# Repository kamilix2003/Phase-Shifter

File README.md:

# Interface for MAPS-010144 digital phase shifter

## Description

STM32G0B01 based board for controlling daisy-chained digital phase shifter via SPI-like serial interface. User can interface with the board either by buttons and LEDs on the board or via virtual serial port over USB, communication over serial port is realized using simple TLV protocol. The board is providing bipolar supply for the phase shifters.

<!--  -->

### Repository contents
- [KiCAD](KiCAD) - ECAD projects of all desinged PCBs for the project
- [python_api](python_api) - Simple python api for communicating with the controller via serial port
- [Src](Src) - Firmware source code separated from generated STM32 project
- [phase_shifter_measurements](phase_shifter_mesurements) - Measuremented scattering parameters of the phase shifter

## Firmware 

<!--  -->

### Serial communication

Available commands:
| **T**ype | **L**ength [bytes] | **V**alue             | Description |
|----------|--------------------|-----------------------|-------------|
| 0x02     | 1                  | command id            | Ack         |
| 0x10     | 4                  | phase shifts (0 - 15) | Set phase   |
| 0x11     | 0                  | -                     | Transmit    |
| 0x12     | 1                  | latch state           | Latch state |

After each message microcontroller should send ACK message with payload containing command id of original message

Example routine to set new phase delay:
1. `0x12 0x01 0x00` - make sure that latch is set low in order to accept data via serial interface
1. `0x10 0x04 0x04 0x02 0x0f 0x08` - send phase shifts to the controller
1. `0x11 0x00` - transmit phase shifts via SPI to the phase shifters
1. `0x12 0x01 0x01` - set latch to update phase shift 
1. `0x12 0x01 0x00` - reset latch

### Buttons and LEDs

The board is equiped in 3 tactile buttons and two 4-led displays where each display shows according to the silkscreen description either currently selected phase shifter or phase shift set for the selected phase shifter.
Buttons have following functions starting from the left most button:
- On short press transmits current phase shifter configuration over SPI
- On short press cycles through 4 phase shifters, on long press sets all phase shifters to 0
- On short press increments phase delay, on long press set current phase shifter to 0

<!-- # MAPS-010144 Phase Shifter Interface as Part of Phased Antenna Array

## Description

A microcontroller serves as an interface for phase control, managing multiple phase shifters connected in a daisy chain via SPI. Bidirectional communication between the PC and MCU is established via UART/USB.

## Goals

in **bold** features in scope of SKM project

- **Serial interface with IC via SPI peripheral**
- **PC-MCU communication by UART/USB (virtual COM)**
- **Controlling multiple phase shifter in daisy chain**
- Python API for controlling beam direction
- I2C bus for communication with multiple arrays where one becomes master

## Block diagram

## Docs

- [Specification](./docs/Specification.md)
- [Report](./docs/SKM_Report_Kamil_Chaj.pdf) -->

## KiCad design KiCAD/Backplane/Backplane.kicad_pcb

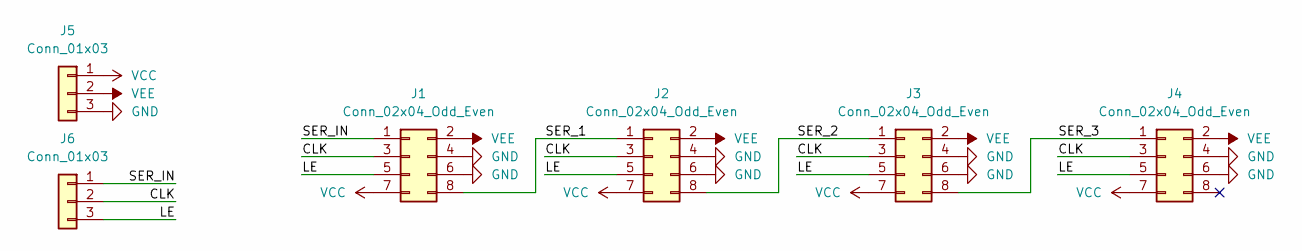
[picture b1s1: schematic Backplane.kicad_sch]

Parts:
J1, J2, J3, J4: Conn_02x04_Odd_Even; PinSocket_2x04_P2.54mm_Vertical
J5, J6: Conn_01x03; PinHeader_1x03_P2.54mm_Horizontal

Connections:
/CLK: J1.3, J2.3, J3.3, J4.3, J6.2
/LE: J1.5, J2.5, J3.5, J4.5, J6.3
/SER_1: J1.8, J2.1
/SER_2: J2.8, J3.1
/SER_3: J3.8, J4.1
/SER_IN: J1.1, J6.1
GND: J1.4, J1.6, J2.4, J2.6, J3.4, J3.6, J4.4, J4.6, J5.3
VCC: J1.7, J2.7, J3.7, J4.7, J5.1
VEE: J1.2, J2.2, J3.2, J4.2, J5.2

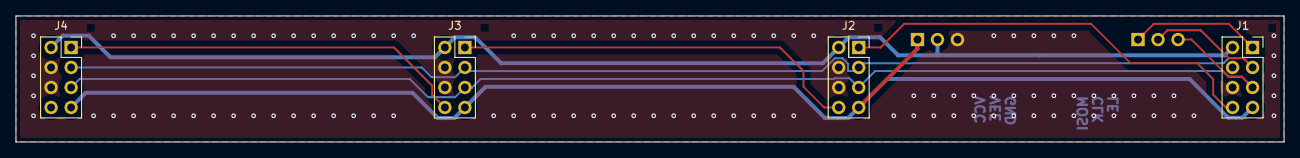
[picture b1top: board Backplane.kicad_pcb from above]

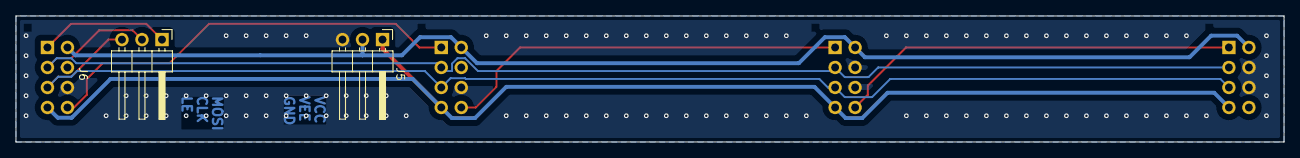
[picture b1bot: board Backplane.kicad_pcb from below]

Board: 2 copper layers, 161.0 x 16.0 mm, 6 parts (2 on the bottom side), 9 nets.

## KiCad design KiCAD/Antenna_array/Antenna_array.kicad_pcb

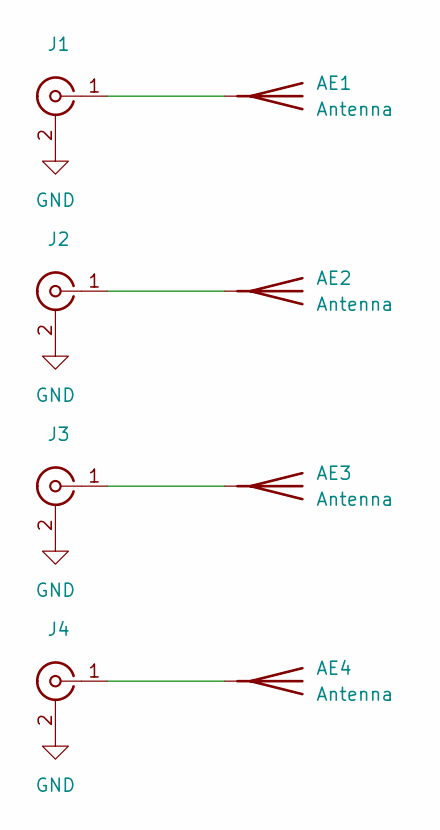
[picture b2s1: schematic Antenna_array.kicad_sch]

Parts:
AE1, AE2, AE3, AE4: Antenna; patch
J1, J2, J3, J4: Conn

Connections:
GND: J1.2, J2.2, J3.2, J4.2
unnamed: AE1.1 (A), J1.1
unnamed: AE2.1 (A), J2.1
unnamed: AE3.1 (A), J3.1
unnamed: AE4.1 (A), J4.1

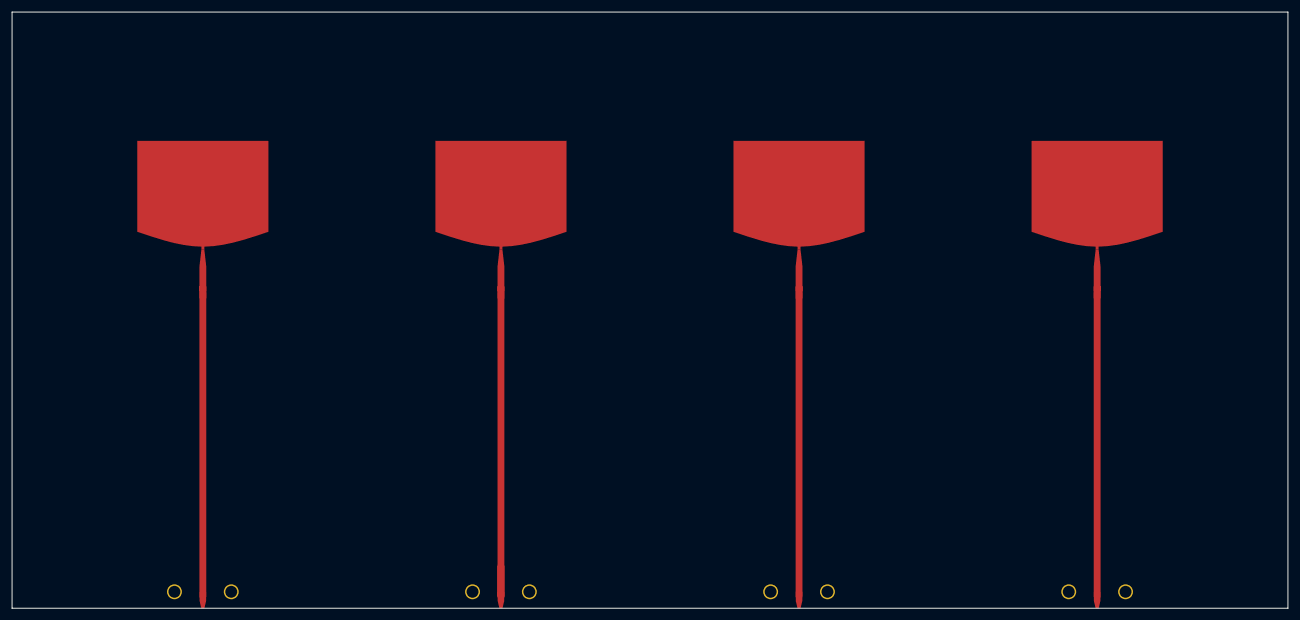
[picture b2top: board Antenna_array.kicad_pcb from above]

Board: 2 copper layers, 214.0 x 100.0 mm, 8 parts (0 on the bottom side), 5 nets.

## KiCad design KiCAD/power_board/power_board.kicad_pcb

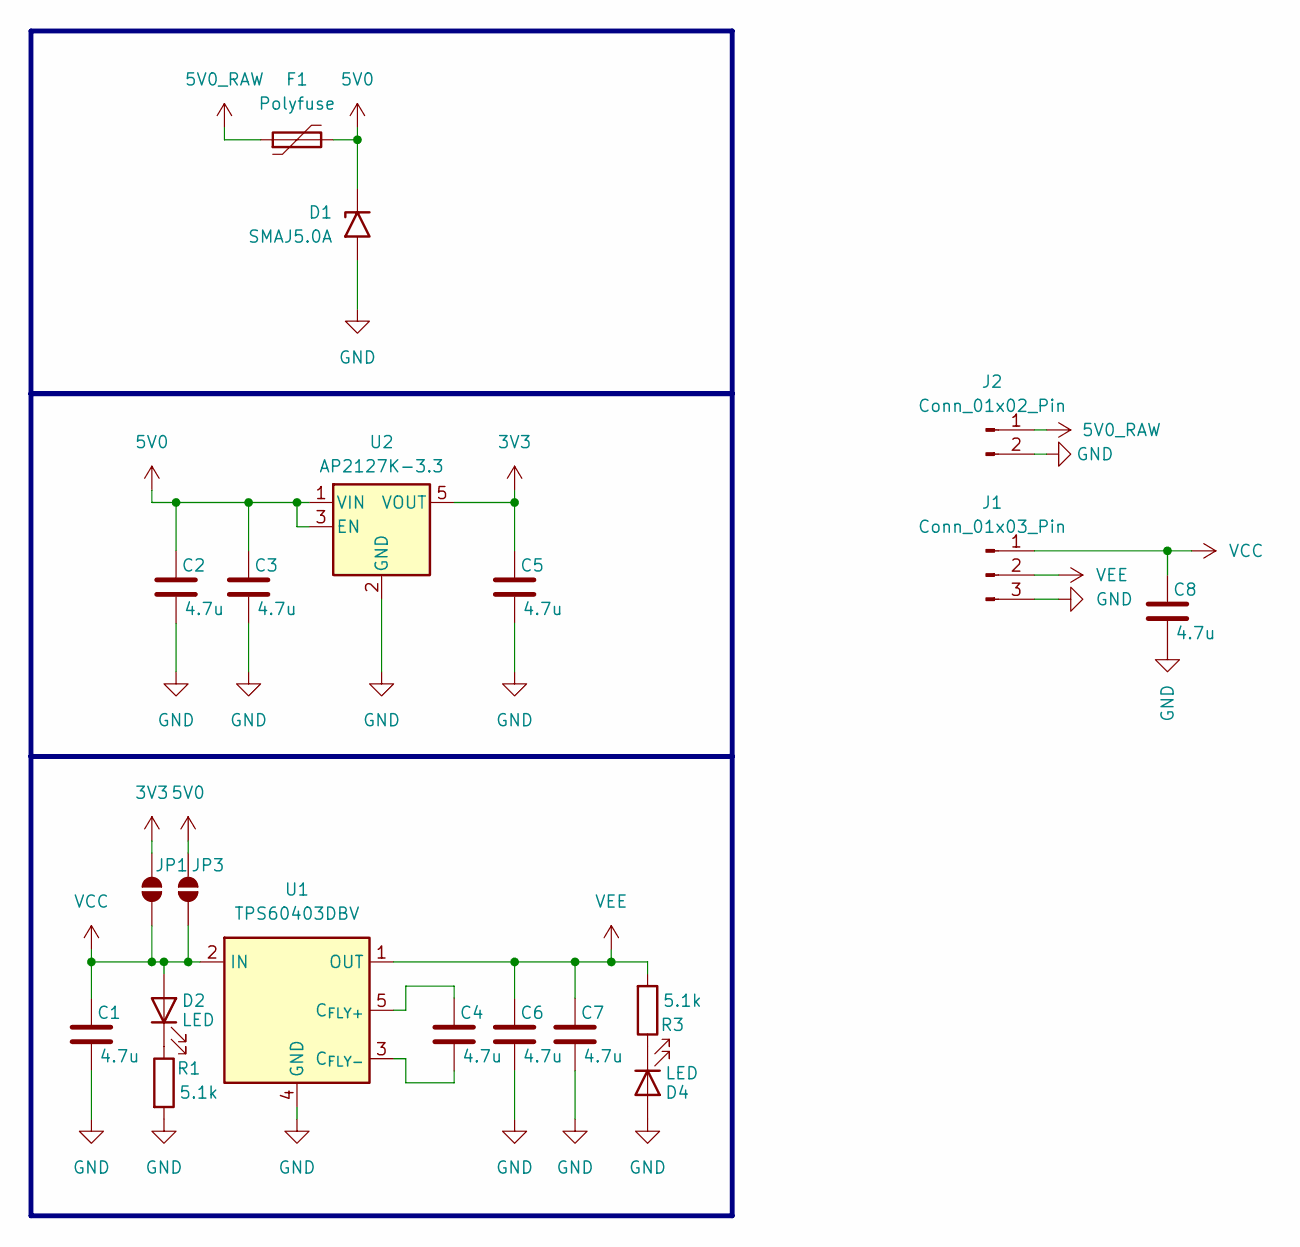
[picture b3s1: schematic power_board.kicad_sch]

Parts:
C1, C2, C3, C4, C5, C6, C7, C8: 4.7u; C_0805_2012Metric_Pad1.18x1.45mm_HandSolder
D1: SMAJ5.0A; D_SMA
D2, D4: LED; LED_0603_1608Metric_Pad1.05x0.95mm_HandSolder
F1: Polyfuse; Fuse_1206_3216Metric_Pad1.42x1.75mm_HandSolder
J1: Conn_01x03_Pin; PinHeader_1x03_P2.54mm_Vertical
J2: Conn_01x02_Pin; PinHeader_1x02_P2.54mm_Vertical
JP1, JP3: SolderJumper_2_Open; SolderJumper-2_P1.3mm_Open_RoundedPad1.0x1.5mm
R1, R3: 5.1k; R_0603_1608Metric_Pad0.98x0.95mm_HandSolder
U1: TPS60403DBV; SOT-23-5
U2: AP2127K-3.3; SOT-23-5

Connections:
3V3: C5.1, JP1.2 (B), U2.5 (VOUT)
5V0: C2.1, C3.1, D1.1 (A1), F1.2, JP3.2 (B), U2.1 (VIN), U2.3 (EN)
5V0_RAW: F1.1, J2.1
GND: C1.2, C2.2, C3.2, C5.2, C6.2, C7.2, C8.2, D1.2 (A2), D4.2 (A), J1.3, J2.2, R1.2, U1.4 (GND), U2.2 (GND)
unnamed: D2.1 (K), R1.1
unnamed: D4.1 (K), R3.1
unnamed: C4.1, U1.5 (C_{FLY+})
unnamed: C4.2, U1.3 (C_{FLY-})
VCC: C1.1, C8.1, D2.2 (A), J1.1, JP1.1 (A), JP3.1 (A), U1.2 (IN)
VEE: C6.1, C7.1, J1.2, R3.2, U1.1 (OUT)

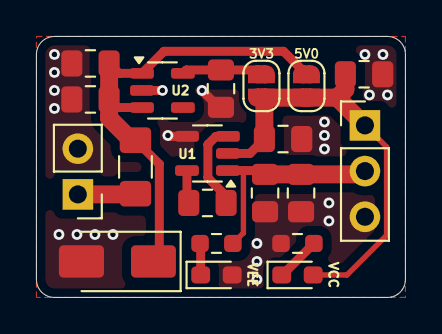
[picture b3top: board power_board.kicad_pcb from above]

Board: 2 copper layers, 20.5 x 14.5 mm, 20 parts (0 on the bottom side), 10 nets.

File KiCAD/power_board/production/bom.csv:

Designator,Footprint,Quantity,Value,LCSC Part #
"C1, C2, C3, C4, C5, C6, C7, C8",0805,8,4.7u,
D1,D_SMA,1,SMAJ5.0A,
"D2, D4",0603,2,LED,
F1,1206,1,Polyfuse,
J1,PinHeader_1x03_P2.54mm_Vertical,1,Conn_01x03_Pin,
J2,PinHeader_1x02_P2.54mm_Vertical,1,Conn_01x02_Pin,
"R1, R3",0603,2,5.1k,
U1,SOT-23-5,1,TPS60403DBV,
U2,SOT-23-5,1,AP2127K-3.3,

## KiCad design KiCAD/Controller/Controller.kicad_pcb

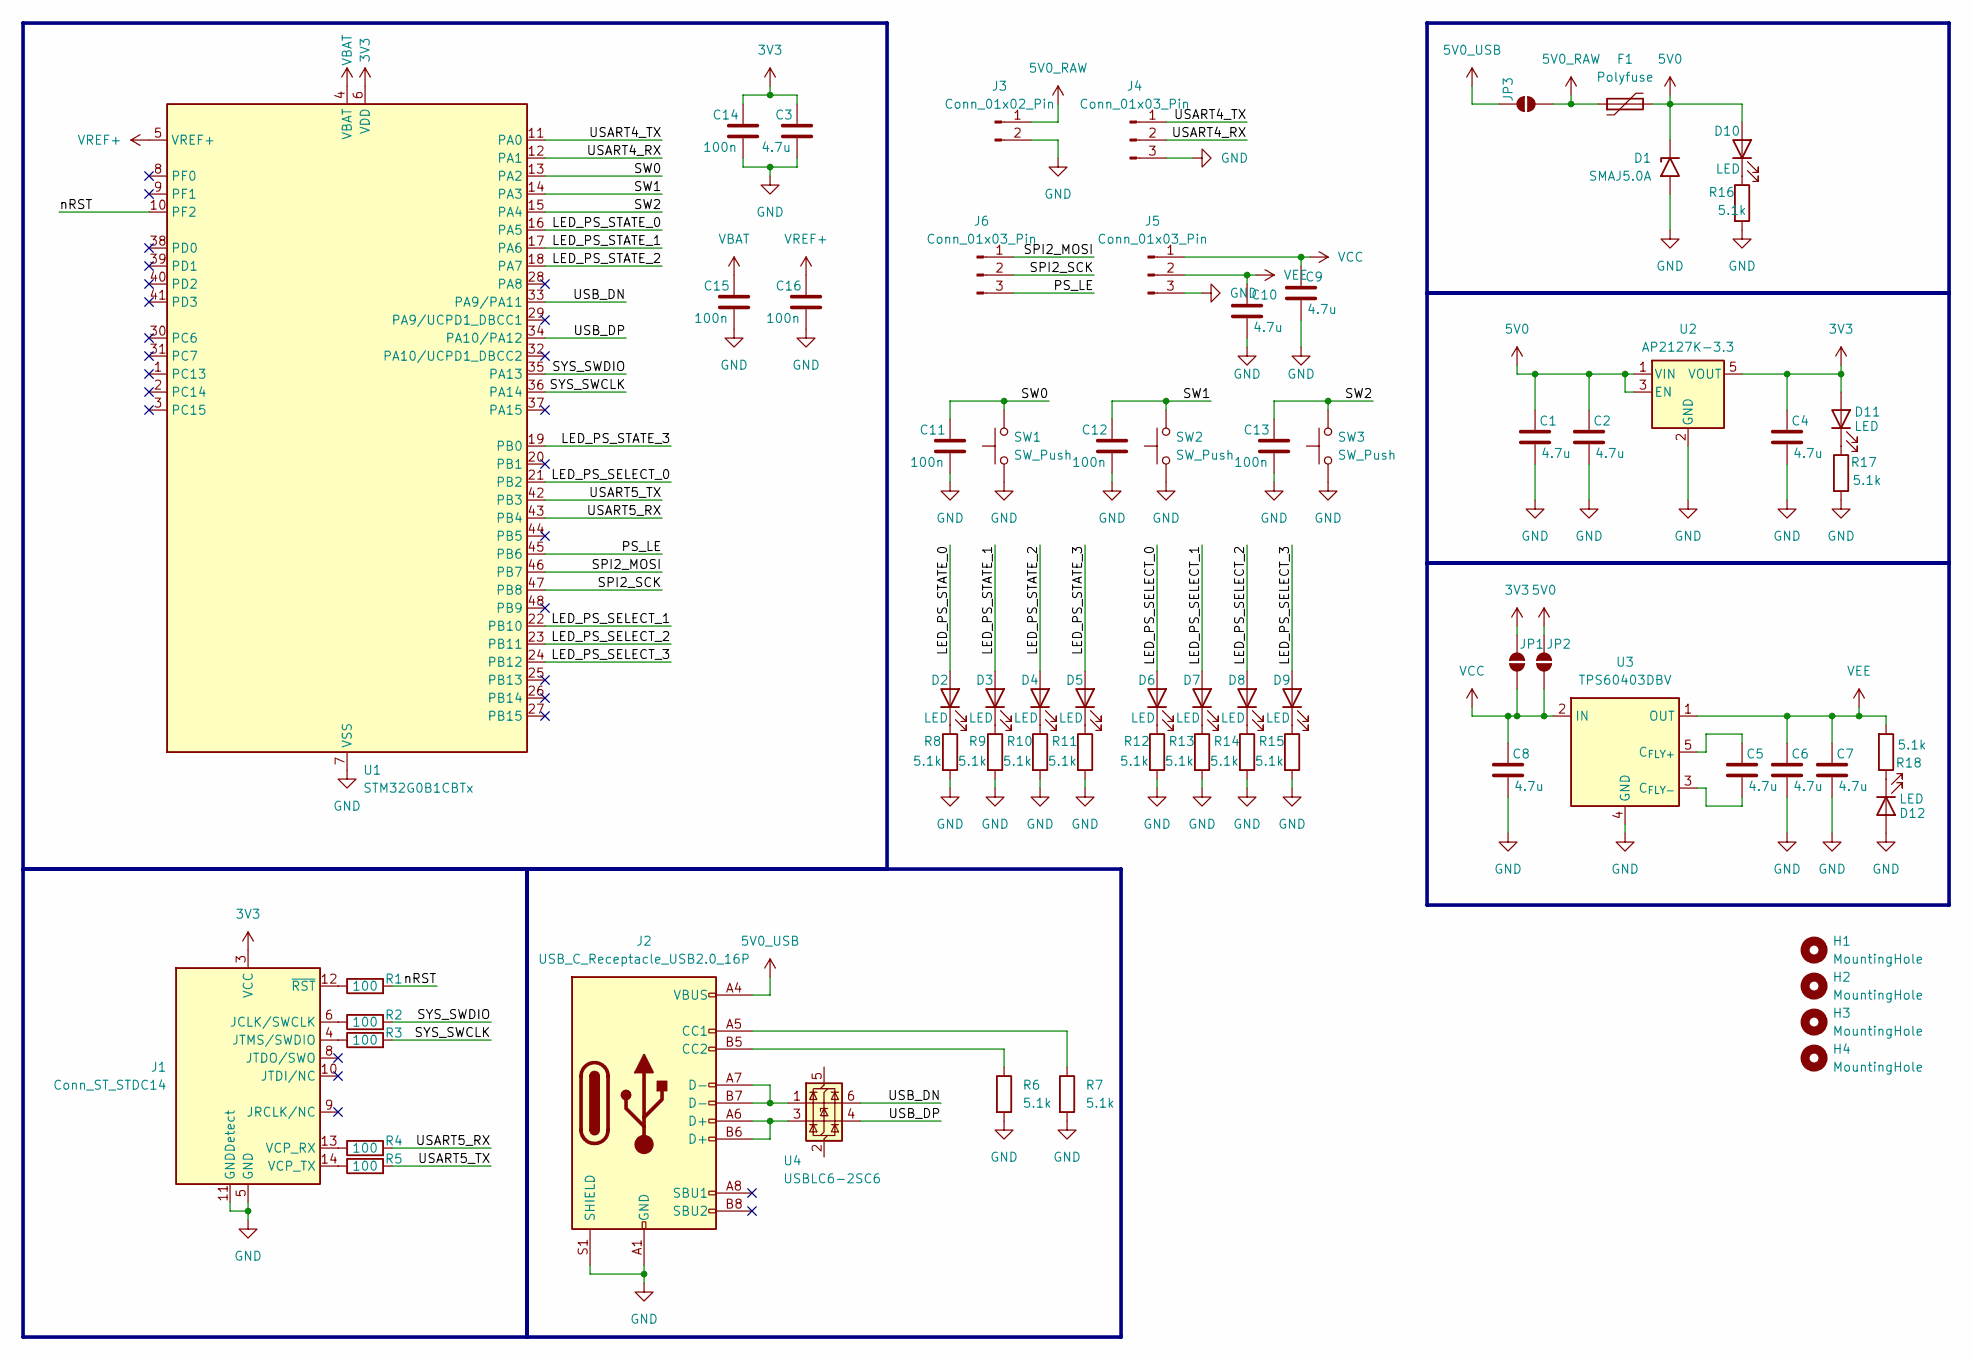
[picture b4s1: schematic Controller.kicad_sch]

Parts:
C1, C2, C3, C4, C5, C6, C7, C8, C9, C10: 4.7u; C_0805_2012Metric_Pad1.18x1.45mm_HandSolder
C11, C12, C13, C14, C15, C16: 100n; C_0603_1608Metric_Pad1.08x0.95mm_HandSolder
D1: SMAJ5.0A; D_SMA
D2, D3, D4, D5, D6, D7, D8, D9, D10, D11, D12: LED; LED_0603_1608Metric_Pad1.05x0.95mm_HandSolder
F1: Polyfuse; Fuse_1206_3216Metric_Pad1.42x1.75mm_HandSolder
H1, H2, H3, H4: MountingHole; MountingHole_3.2mm_M3
J1: Conn_ST_STDC14; PinHeader_2x07_P1.27mm_Vertical
J2: USB_C_Receptacle_USB2.0_16P; USB_C_Receptacle_GCT_USB4105-xx-A_16P_TopMnt_Horizontal
J3: Conn_01x02_Pin; PinHeader_1x02_P2.54mm_Vertical
J4, J5, J6: Conn_01x03_Pin; PinHeader_1x03_P2.54mm_Vertical
JP1, JP2, JP3: SolderJumper_2_Open; SolderJumper-2_P1.3mm_Open_RoundedPad1.0x1.5mm
R1, R2, R3, R4, R5: 100; R_0603_1608Metric_Pad0.98x0.95mm_HandSolder
R6, R7, R8, R9, R10, R11, R12, R13, R14, R15, R16, R17, R18: 5.1k; R_0603_1608Metric_Pad0.98x0.95mm_HandSolder
SW1, SW2, SW3: SW_Push; SW_SPST_PTS647_Sx38
U1: STM32G0B1CBTx; LQFP-48_7x7mm_P0.5mm
U2: AP2127K-3.3; SOT-23-5
U3: TPS60403DBV; SOT-23-5
U4: USBLC6-2SC6; SOT-23-6

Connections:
3V3: C3.1, C4.1, C14.1, D11.2 (A), J1.3 (VCC), JP1.2 (B), U1.6 (VDD), U2.5 (VOUT)
5V0: C1.1, C2.1, D1.1 (A1), D10.2 (A), F1.2, JP2.2 (B), U2.1 (VIN), U2.3 (EN)
5V0_RAW: F1.1, J3.1, JP3.1 (A)
5V0_USB: J2.A4 (VBUS), J2.A9 (VBUS), J2.B4 (VBUS), J2.B9 (VBUS), JP3.2 (B)
/LED_PS_SELECT_0: D6.2 (A), U1.21 (PB2)
/LED_PS_SELECT_1: D7.2 (A), U1.22 (PB10)
/LED_PS_SELECT_2: D8.2 (A), U1.23 (PB11)
/LED_PS_SELECT_3: D9.2 (A), U1.24 (PB12)
/LED_PS_STATE_0: D2.2 (A), U1.16 (PA5)
/LED_PS_STATE_1: D3.2 (A), U1.17 (PA6)
/LED_PS_STATE_2: D4.2 (A), U1.18 (PA7)
/LED_PS_STATE_3: D5.2 (A), U1.19 (PB0)
/PS_LE: J6.3, U1.45 (PB6)
/SPI2_MOSI: J6.1, U1.46 (PB7)
/SPI2_SCK: J6.2, U1.47 (PB8)
/SW0: C11.1, SW1.2, U1.13 (PA2)
/SW1: C12.1, SW2.2, U1.14 (PA3)
/SW2: C13.1, SW3.2, U1.15 (PA4)
/SYS_SWCLK: R3.2, U1.36 (PA14)
/SYS_SWDIO: R2.2, U1.35 (PA13)
/USART4_RX: J4.2, U1.12 (PA1)
/USART4_TX: J4.1, U1.11 (PA0)
/USART5_RX: R4.2, U1.43 (PB4)
/USART5_TX: R5.2, U1.42 (PB3)
/USB_DN: U1.33 (PA9/PA11), U4.6 (I/O1)
/USB_DP: U1.34 (PA10/PA12), U4.4 (I/O2)
/nRST: R1.2, U1.10 (PF2)
GND: C1.2, C2.2, C3.2, C4.2, C6.2, C7.2, C8.2, C9.2, C10.2, C11.2, C12.2, C13.2, C14.2, C15.2, C16.2, D1.2 (A2), D12.2 (A), J1.5 (GND), J1.7 (GND), J1.11 (GNDDetect), J2.A1 (GND), J2.A12 (GND), J2.B1 (GND), J2.B12 (GND), J2.S1 (SHIELD), J3.2, J4.3, J5.3, R6.2, R7.2, R8.2, R9.2, R10.2, R11.2, R12.2, R13.2, R14.2, R15.2, R16.2, R17.2, SW1.1, SW2.1, SW3.1, U1.7 (VSS), U2.2 (GND), U3.4 (GND)
unnamed: D2.1 (K), R8.1
unnamed: D3.1 (K), R9.1
unnamed: D4.1 (K), R10.1
unnamed: D5.1 (K), R11.1
unnamed: D6.1 (K), R12.1
unnamed: D7.1 (K), R13.1
unnamed: D8.1 (K), R14.1
unnamed: D9.1 (K), R15.1
unnamed: D10.1 (K), R16.1
unnamed: D11.1 (K), R17.1
unnamed: D12.1 (K), R18.1
unnamed: J1.6 (JCLK/SWCLK), R2.1
unnamed: J1.4 (JTMS/SWDIO), R3.1
unnamed: J1.13 (VCP_RX), R4.1
unnamed: J1.14 (VCP_TX), R5.1
unnamed: J1.12 (~RST), R1.1
unnamed: J2.A5 (CC1), R7.1
unnamed: J2.B5 (CC2), R6.1
unnamed: J2.A6 (D+), J2.B6 (D+), U4.3 (I/O2)
unnamed: J2.A7 (D-), J2.B7 (D-), U4.1 (I/O1)
unnamed: C5.1, U3.5 (C_{FLY+})
unnamed: C5.2, U3.3 (C_{FLY-})
VBAT: C15.1, U1.4 (VBAT)
VCC: C8.1, C9.1, J5.1, JP1.1 (A), JP2.1 (A), U3.2 (IN)
VEE: C6.1, C7.1, C10.1, J5.2, R18.2, U3.1 (OUT)
VREF+: C16.1, U1.5 (VREF+)

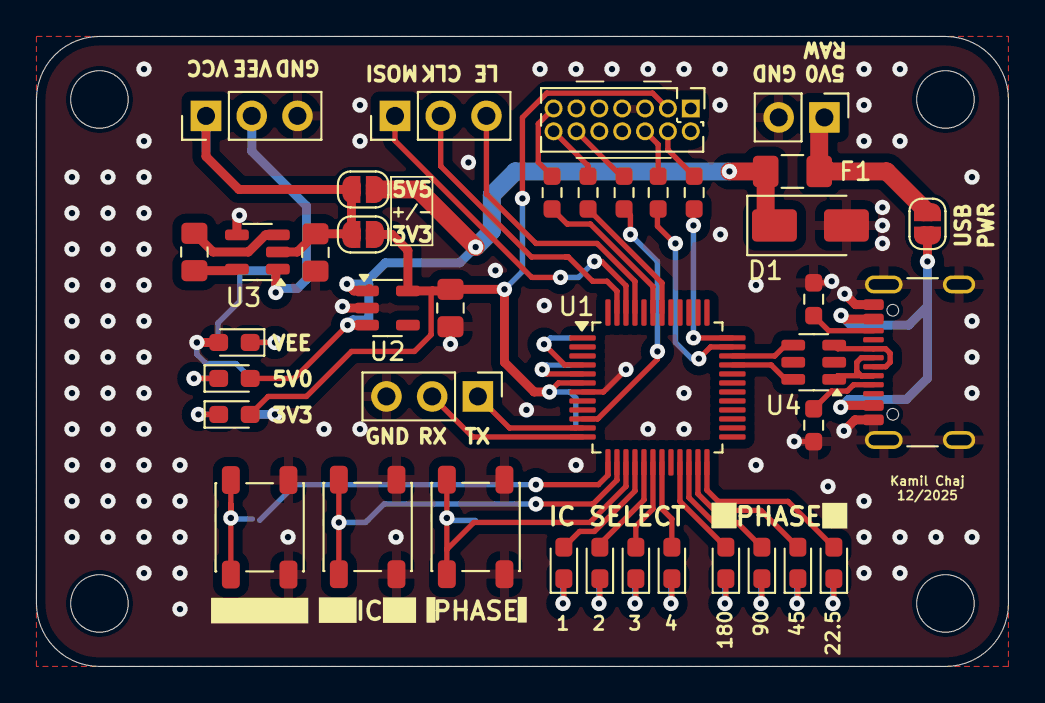
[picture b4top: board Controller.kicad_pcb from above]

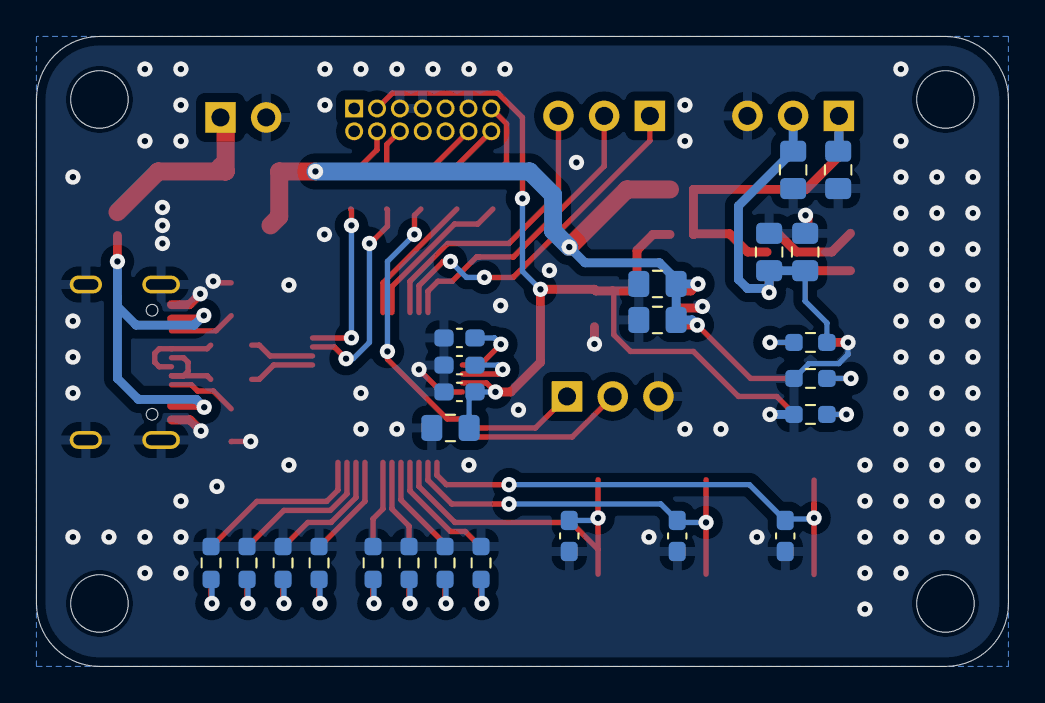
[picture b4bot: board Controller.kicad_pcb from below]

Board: 2 copper layers, 54.0 x 35.0 mm, 67 parts (24 on the bottom side), 54 nets.

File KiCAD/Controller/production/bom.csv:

Designator,Footprint,Quantity,Value,LCSC Part #
"C1, C10, C2, C3, C4, C5, C6, C7, C8, C9",0805,10,4.7u,
"C11, C12, C13, C14, C15, C16",0603,6,100n,
D1,D_SMA,1,SMAJ5.0A,
"D10, D11, D12, D2, D3, D4, D5, D6, D7, D8, D9",0603,11,LED,
F1,1206,1,Polyfuse,
J1,PinHeader_2x07_P1.27mm_Vertical,1,Conn_ST_STDC14,
J2,USB_C_Receptacle_GCT_USB4105-xx-A_16P_TopMnt_Horizontal,1,USB_C_Receptacle_USB2.0_16P,
J3,PinHeader_1x02_P2.54mm_Vertical,1,Conn_01x02_Pin,
"J4, J5, J6",PinHeader_1x03_P2.54mm_Vertical,3,Conn_01x03_Pin,
"R1, R2, R3, R4, R5",0603,5,100,
"R10, R11, R12, R13, R14, R15, R16, R17, R18, R6, R7, R8, R9",0603,13,5.1k,
"SW1, SW2, SW3",SW_SPST_PTS647_Sx38,3,SW_Push,
U1,LQFP-48_7x7mm_P0.5mm,1,STM32G0B1CBTx,
U2,SOT-23-5,1,AP2127K-3.3,
U3,SOT-23-5,1,TPS60403DBV,
U4,SOT-23-6,1,USBLC6-2SC6,

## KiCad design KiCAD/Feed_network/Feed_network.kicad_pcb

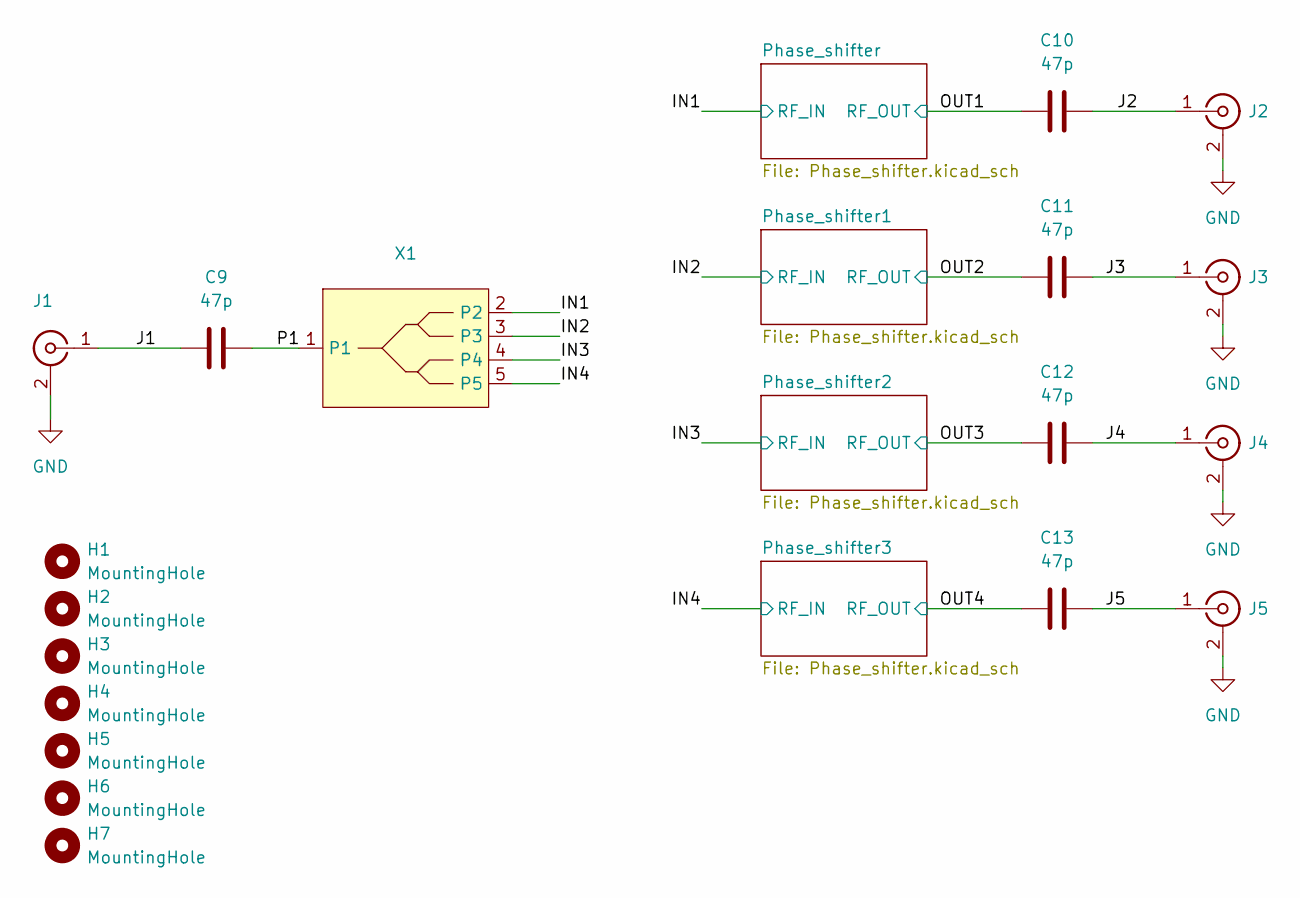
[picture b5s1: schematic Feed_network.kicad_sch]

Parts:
C9, C10, C11, C12, C13: 47p; C_0603_1608Metric_Pad1.08x0.95mm_HandSolder
H1, H2, H3, H4, H5, H6, H7: MountingHole; MountingHole_3.2mm_M3
J1, J2, J3, J4, J5: Conn
X1: 4_way_divider

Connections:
/IN1: X1.2; also elsewhere on the board
/IN2: X1.3; also elsewhere on the board
/IN3: X1.4; also elsewhere on the board
/IN4: X1.5; also elsewhere on the board
/J1: C9.1, J1.1
/J2: C10.1, J2.1
/J3: C11.1, J3.1
/J4: C12.1, J4.1
/J5: C13.1, J5.1
/OUT1: C10.2; also elsewhere on the board
/OUT2: C11.2; also elsewhere on the board
/OUT3: C12.2; also elsewhere on the board
/OUT4: C13.2; also elsewhere on the board
/P1: C9.2, X1.1
GND: J1.2, J2.2, J3.2, J4.2, J5.2; also elsewhere on the board

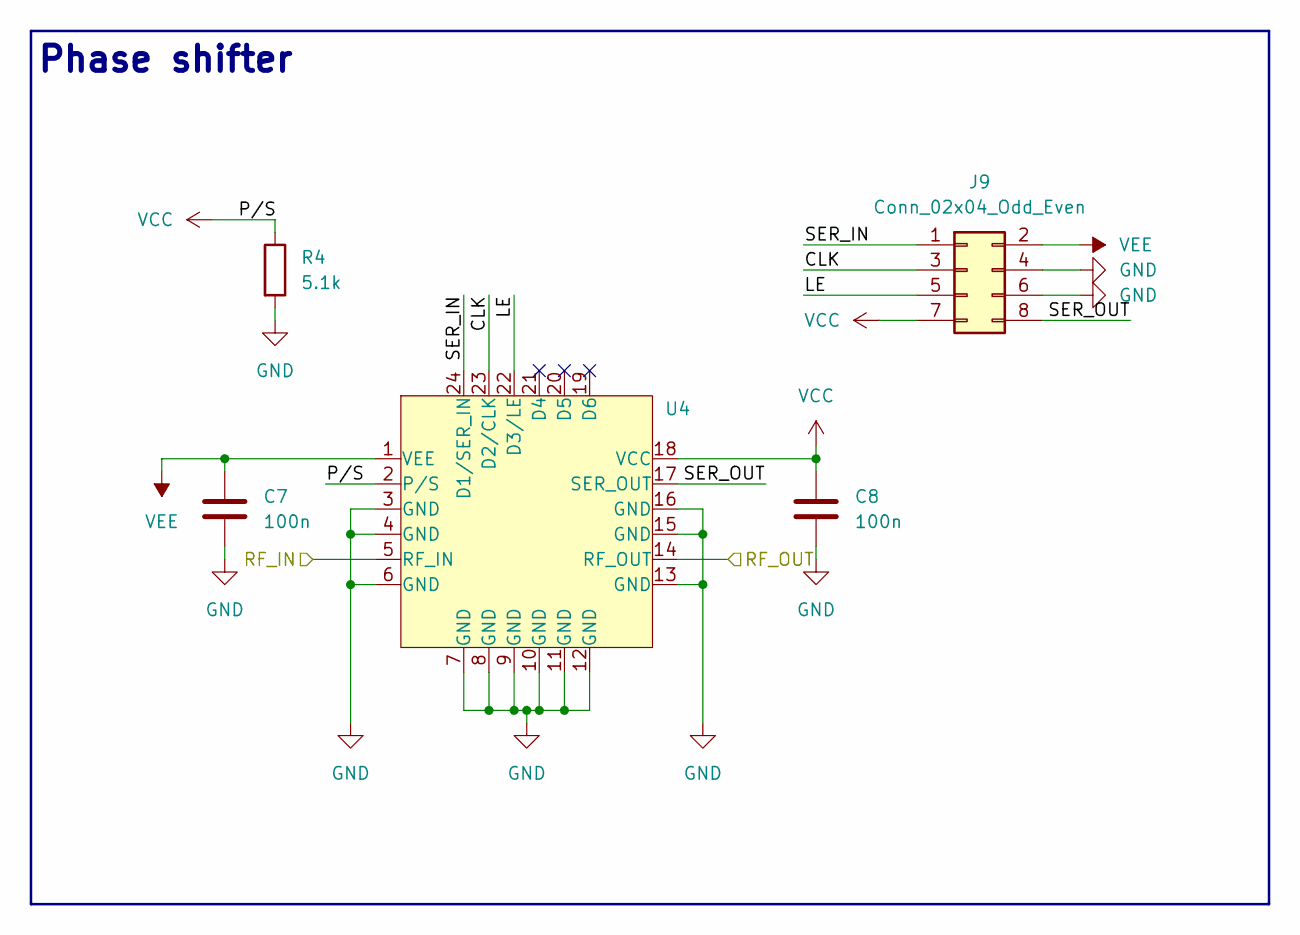
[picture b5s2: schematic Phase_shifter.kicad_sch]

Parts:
C7, C8: 100n; C_0603_1608Metric_Pad1.08x0.95mm_HandSolder
J9: Conn_02x04_Odd_Even; PinHeader_2x04_P2.54mm_Vertical
R4: 5.1k; R_0603_1608Metric_Pad0.98x0.95mm_HandSolder
U4: QFN-24_EP_4x4_Pitch0.5mm

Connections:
/IN4: U4.5 (RF_IN); also elsewhere on the board
/OUT4: U4.14 (RF_OUT); also elsewhere on the board
/Phase_shifter3/CLK: J9.3, U4.23 (D2/CLK)
/Phase_shifter3/LE: J9.5, U4.22 (D3/LE)
/Phase_shifter3/SER_IN: J9.1, U4.24 (D1/SER_IN)
/Phase_shifter3/SER_OUT: J9.8, U4.17 (SER_OUT)
GND: C7.2, C8.2, J9.4, J9.6, R4.2, U4.3 (GND), U4.4 (GND), U4.6 (GND), U4.7 (GND), U4.8 (GND), U4.9 (GND), U4.10 (GND), U4.11 (GND), U4.12 (GND), U4.13 (GND), U4.15 (GND), U4.16 (GND); also elsewhere on the board
VCC: C8.1, J9.7, R4.1, U4.2 (P/S), U4.18 (VCC); also elsewhere on the board
VEE: C7.1, J9.2, U4.1 (VEE); also elsewhere on the board

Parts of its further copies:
C1, C2, C3, C4, C5, C6: 100n; C_0603_1608Metric_Pad1.08x0.95mm_HandSolder
J6, J7, J8: Conn_02x04_Odd_Even; PinHeader_2x04_P2.54mm_Vertical
R1, R2, R3: 5.1k; R_0603_1608Metric_Pad0.98x0.95mm_HandSolder
U1, U2, U3: QFN-24_EP_4x4_Pitch0.5mm

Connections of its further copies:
/IN1: U1.5 (RF_IN); also elsewhere on the board
/IN2: U2.5 (RF_IN); also elsewhere on the board
/IN3: U3.5 (RF_IN); also elsewhere on the board
/OUT1: U1.14 (RF_OUT); also elsewhere on the board
/OUT2: U2.14 (RF_OUT); also elsewhere on the board
/OUT3: U3.14 (RF_OUT); also elsewhere on the board
/Phase_shifter1/CLK: J7.3, U2.23 (D2/CLK)
/Phase_shifter1/LE: J7.5, U2.22 (D3/LE)
/Phase_shifter1/SER_IN: J7.1, U2.24 (D1/SER_IN)
/Phase_shifter1/SER_OUT: J7.8, U2.17 (SER_OUT)
/Phase_shifter2/CLK: J8.3, U3.23 (D2/CLK)
/Phase_shifter2/LE: J8.5, U3.22 (D3/LE)
/Phase_shifter2/SER_IN: J8.1, U3.24 (D1/SER_IN)
/Phase_shifter2/SER_OUT: J8.8, U3.17 (SER_OUT)
/Phase_shifter/CLK: J6.3, U1.23 (D2/CLK)
/Phase_shifter/LE: J6.5, U1.22 (D3/LE)
/Phase_shifter/SER_IN: J6.1, U1.24 (D1/SER_IN)
/Phase_shifter/SER_OUT: J6.8, U1.17 (SER_OUT)
GND: C1.2, C2.2, C3.2, C4.2, C5.2, C6.2, J6.4, J6.6, J7.4, J7.6, J8.4, J8.6, R1.2, R2.2, R3.2, U1.3 (GND), U1.4 (GND), U1.6 (GND), U1.7 (GND), U1.8 (GND), U1.9 (GND), U1.10 (GND), U1.11 (GND), U1.12 (GND), U1.13 (GND), U1.15 (GND), U1.16 (GND), U2.3 (GND), U2.4 (GND), U2.6 (GND), U2.7 (GND), U2.8 (GND), U2.9 (GND), U2.10 (GND), U2.11 (GND), U2.12 (GND), U2.13 (GND), U2.15 (GND), U2.16 (GND), U3.3 (GND), U3.4 (GND), U3.6 (GND), U3.7 (GND), U3.8 (GND), U3.9 (GND), U3.10 (GND), U3.11 (GND), U3.12 (GND), U3.13 (GND), U3.15 (GND), U3.16 (GND); also elsewhere on the board
VCC: C2.1, C4.1, C6.1, J6.7, J7.7, J8.7, R1.1, R2.1, R3.1, U1.2 (P/S), U1.18 (VCC), U2.2 (P/S), U2.18 (VCC), U3.2 (P/S), U3.18 (VCC); also elsewhere on the board
VEE: C1.1, C3.1, C5.1, J6.2, J7.2, J8.2, U1.1 (VEE), U2.1 (VEE), U3.1 (VEE); also elsewhere on the board

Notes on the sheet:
Phase shifter

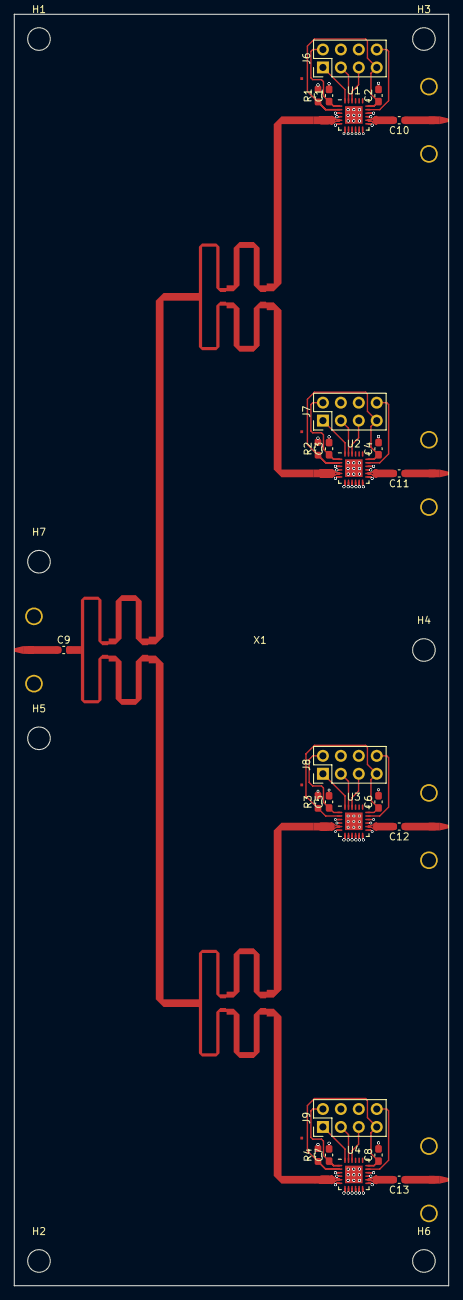
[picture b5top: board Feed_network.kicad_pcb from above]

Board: 2 copper layers, 61.5 x 180.0 mm, 38 parts (0 on the bottom side), 33 nets.

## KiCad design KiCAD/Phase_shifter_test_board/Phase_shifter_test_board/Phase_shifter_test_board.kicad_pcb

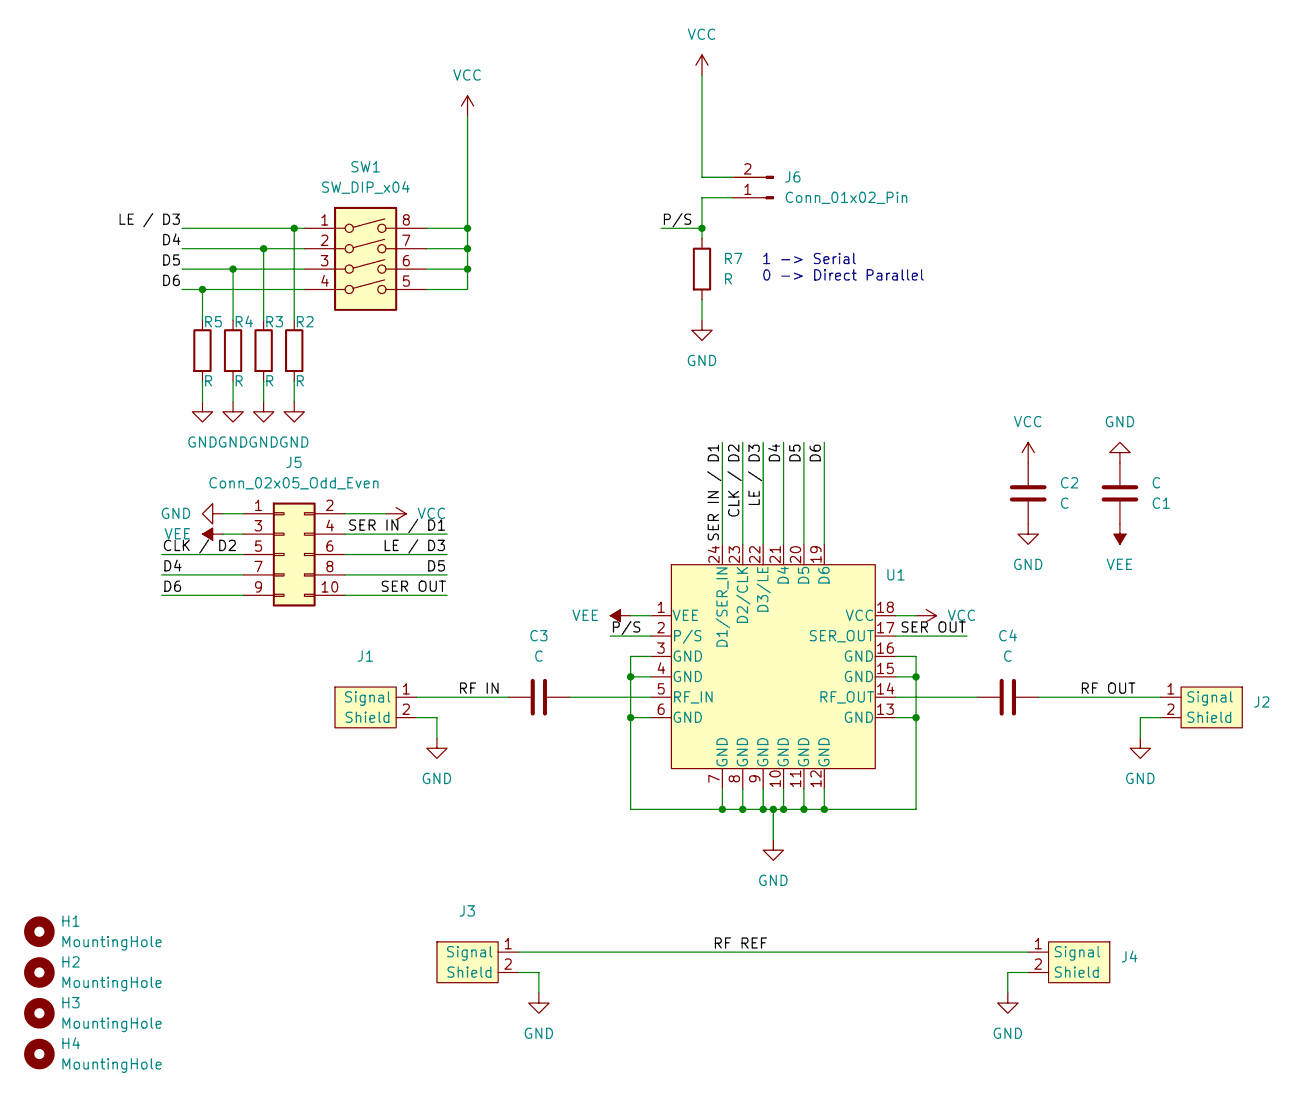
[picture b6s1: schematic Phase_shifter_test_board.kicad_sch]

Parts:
C1, C2, C3, C4: C; C_0603_1608Metric_Pad1.08x0.95mm_HandSolder
H1, H2, H3, H4: MountingHole; MountingHole_3.2mm_M3
J1, J2, J3, J4: Conn
J5: Conn_02x05_Odd_Even; PinHeader_2x05_P2.54mm_Vertical
J6: Conn_01x02_Pin; PinHeader_1x02_P2.54mm_Vertical
R2, R3, R4, R5, R7: R; R_0603_1608Metric_Pad0.98x0.95mm_HandSolder
SW1: SW_DIP_x04; SW_DIP_SPSTx04_Slide_9.78x12.34mm_W7.62mm_P2.54mm
U1: QFN-24_EP_4x4_Pitch0.5mm

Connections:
/CLK / D2: J5.5, U1.23 (D2/CLK)
/D4: J5.7, R3.1, SW1.2, U1.21 (D4)
/D5: J5.8, R4.1, SW1.3, U1.20 (D5)
/D6: J5.9, R5.1, SW1.4, U1.19 (D6)
/LE / D3: J5.6, R2.1, SW1.1, U1.22 (D3/LE)
/P/S: J6.1, R7.1, U1.2 (P/S)
/RF IN: C3.1, J1.1 (Signal)
/RF OUT: C4.2, J2.1 (Signal)
/RF REF: J3.1 (Signal), J4.1 (Signal)
/SER IN / D1: J5.4, U1.24 (D1/SER_IN)
/SER OUT: J5.10, U1.17 (SER_OUT)
GND: C1.2, C2.2, J1.2 (Shield), J2.2 (Shield), J3.2 (Shield), J4.2 (Shield), J5.1, R2.2, R3.2, R4.2, R5.2, R7.2, U1.3 (GND), U1.4 (GND), U1.6 (GND), U1.7 (GND), U1.8 (GND), U1.9 (GND), U1.10 (GND), U1.11 (GND), U1.12 (GND), U1.13 (GND), U1.15 (GND), U1.16 (GND)
unnamed: C3.2, U1.5 (RF_IN)
unnamed: C4.1, U1.14 (RF_OUT)
VCC: C2.1, J5.2, J6.2, SW1.5, SW1.6, SW1.7, SW1.8, U1.18 (VCC)
VEE: C1.1, J5.3, U1.1 (VEE)

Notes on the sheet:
1 -> Serial 0 -> Direct Parallel

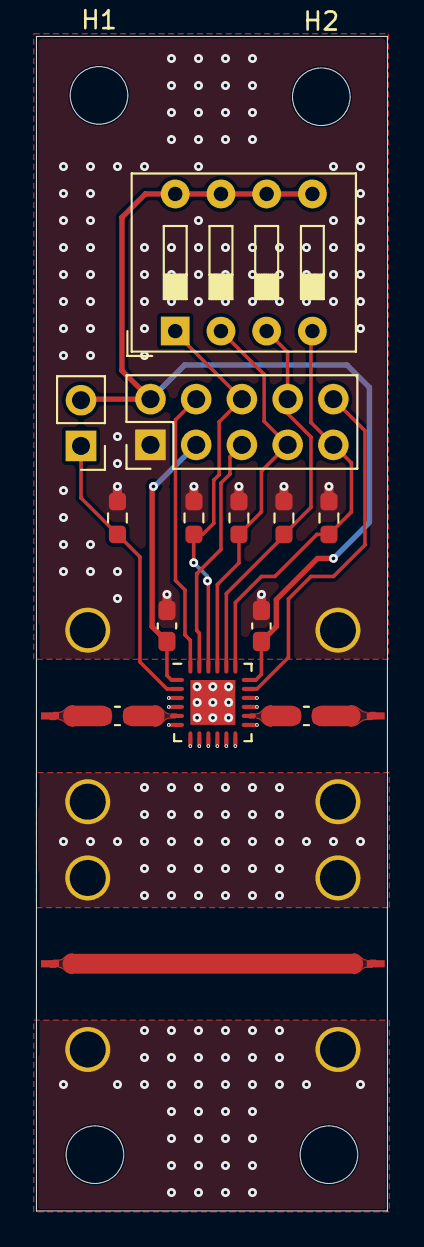
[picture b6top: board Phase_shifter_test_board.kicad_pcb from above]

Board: 2 copper layers, 19.5 x 65.2 mm, 21 parts (0 on the bottom side), 16 nets.

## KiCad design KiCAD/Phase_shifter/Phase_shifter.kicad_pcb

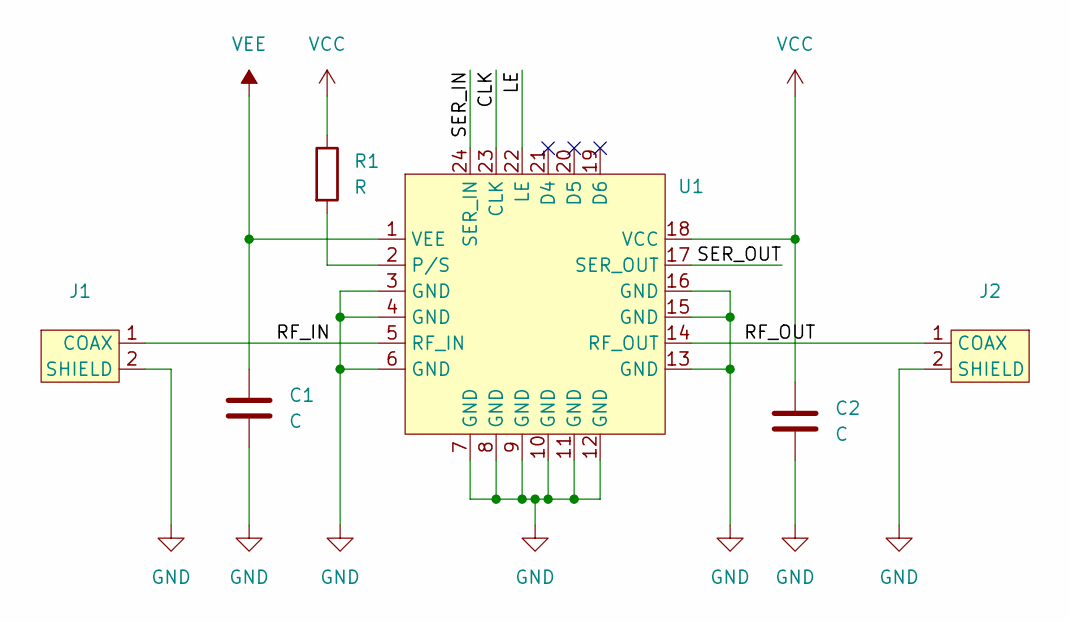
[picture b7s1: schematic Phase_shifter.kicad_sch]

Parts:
C1, C2: C; C_0603_1608Metric_Pad1.08x0.95mm_HandSolder
J1, J2: Connector
R1: R; R_0603_1608Metric_Pad0.98x0.95mm_HandSolder
U1: MAPS-010144

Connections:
/CLK: U1.23 (CLK)
/LE: U1.22 (LE)
/SER_IN: U1.24 (SER_IN)
/SER_OUT: U1.17 (SER_OUT)
GND: C1.2, C2.2, J1.2 (SHIELD), J2.2 (SHIELD), U1.3 (GND), U1.4 (GND), U1.6 (GND), U1.7 (GND), U1.8 (GND), U1.9 (GND), U1.10 (GND), U1.11 (GND), U1.12 (GND), U1.13 (GND), U1.15 (GND), U1.16 (GND)
unnamed: J1.1 (COAX), U1.5 (RF_IN)
unnamed: J2.1 (COAX), U1.14 (RF_OUT)
unnamed: R1.2, U1.2 (P/S)
VCC: C2.1, R1.1, U1.18 (VCC)
VEE: C1.1, U1.1 (VEE)

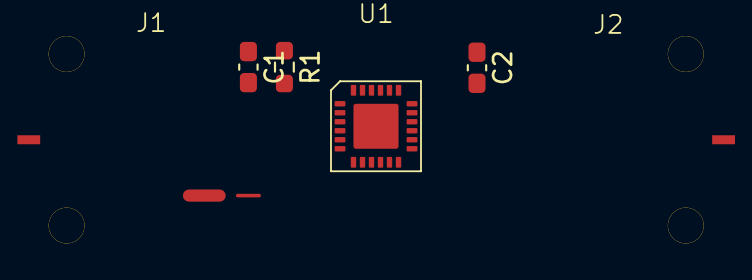
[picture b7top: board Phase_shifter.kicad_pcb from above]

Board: 2 copper layers, 6 parts (0 on the bottom side), 6 nets.

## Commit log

2025-05-13 Update README and add detailed specification for Phase Shifter Interface
2025-05-15 stm32 project
2025-05-20 minor update
2025-06-01 HELP :(
2025-06-26 basic spi, cmake
2025-06-26 LE issues
2025-06-27 phase shifter interface
2025-06-27 Initial UART communication
2025-06-28 basic spi interfaceing
2025-06-29 python API
2025-06-30 DONE :)
2025-09-16 phase shifter
2025-09-24 test board
2025-09-28 skeleton
2025-09-30 python interface refactor
2025-10-13 miorer update
2025-10-21 measurements
2025-11-21 text mode
2025-12-17 Working and tested
2025-12-20 all changed files in d5
2026-03-01 recreated project
2026-03-09 remake
2026-03-11 soft timer tested
2026-03-13 debug
2026-03-14 operation queue
2026-03-16 led indicator
2026-03-17 com interface
2026-03-18 com interface debug
2026-04-01 serial interface
2026-04-07 partial readme
2026-04-10 readme
2026-04-10 Board bring up (#2)
    * recreated project
    * remake
    * soft timer tested
    * debug
    * operation queue
    * led indicator
2026-04-11 Fix typo in phase shifter measurements section
    Corrected a typo in the phase shifter measurements link.
